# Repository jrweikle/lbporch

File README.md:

# lbporch
This is my attempt to clone the Orch90 board for the TRS80 Model 3 and 4 
it is a work in progress it has not been tested on a machine at this time

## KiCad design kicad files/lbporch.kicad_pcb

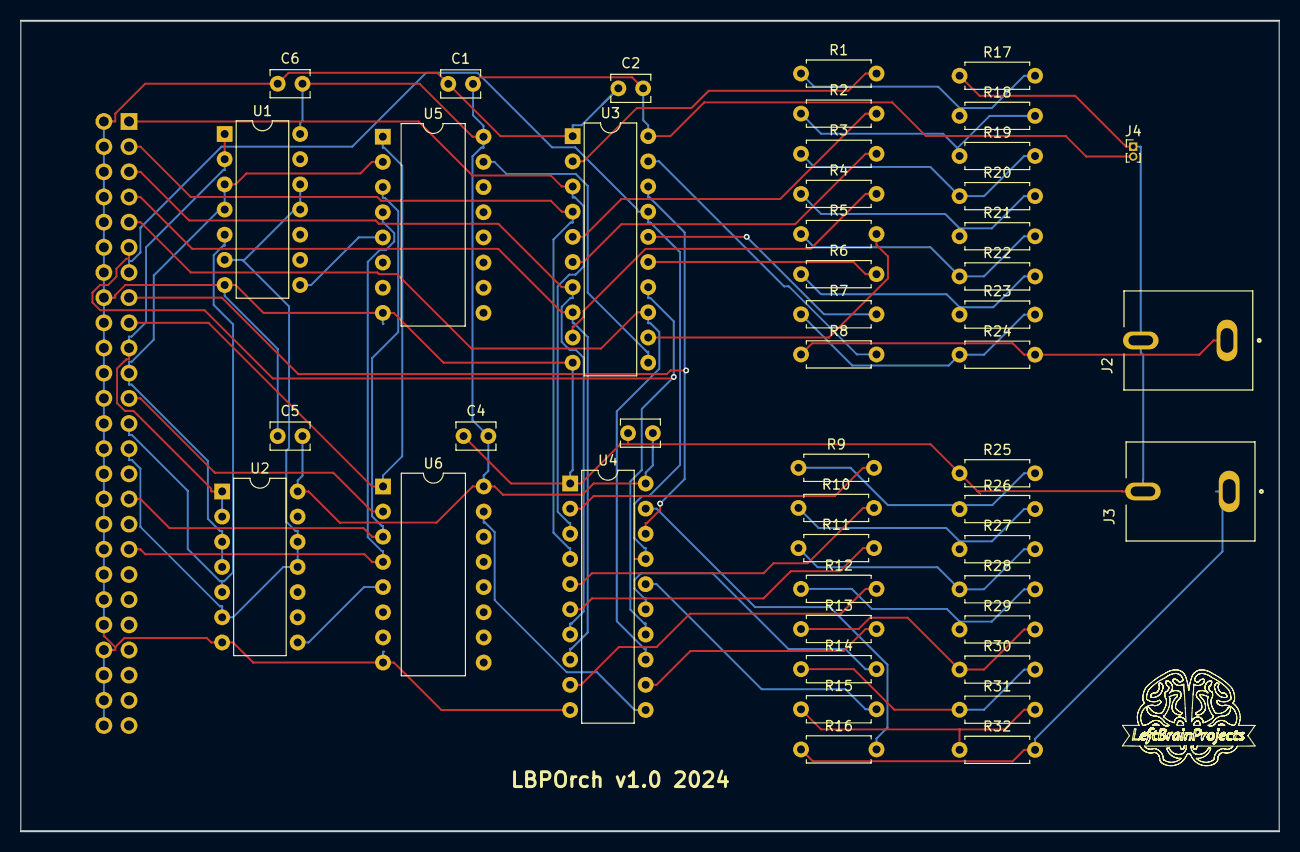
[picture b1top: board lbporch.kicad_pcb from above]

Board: 2 copper layers, 127.0 x 81.8 mm, 48 parts (1 on the bottom side), 54 nets.

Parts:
C1, C2, C3, C4, C5, C6: 0.1; C_Disc_D3.8mm_W2.6mm_P2.50mm
J1: Conn_02x25_Odd_Even; PinHeader_2x25_P2.54mm_Vertical
J2, J3: Conn_Coaxial; CUI_RCJ-054
J4: Conn_01x02_Pin; PinHeader_1x02_P1.00mm_Vertical
R1, R2, R3, R4, R5, R6, R7, R8, R9, R10, R11, R12, R13, R14, R15, R16: 20k; R_Axial_DIN0207_L6.3mm_D2.5mm_P7.62mm_Horizontal
R17, R18, R19, R20, R21, R22, R23, R24, R25, R26, R27, R28, R29, R30, R31, R32: 10k; R_Axial_DIN0207_L6.3mm_D2.5mm_P7.62mm_Horizontal
U1, U2: 74LS30; DIP-14_W7.62mm
U3, U4: 74LS374; DIP-20_W7.62mm
U5, U6: 74LS138; DIP-16_W10.16mm

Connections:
+5V: C1.2, C2.2, C3.2, C4.2, C5.2, C6.2, J4.2, U1.14 (Vcc), U2.14 (Vcc), U3.20 (VCC), U4.20 (VCC), U5.16 (VCC), U6.16 (VCC)
/A0: J1.17, U5.1 (A0), U6.1 (A0)
/A1: J1.19, U1.1, U1.2, U2.1, U2.2
/A2: J1.21, U1.3, U1.4, U2.3, U2.4, U5.2 (A1)
/A3: J1.23, U6.2 (A1)
/A4: J1.25, U1.5, U2.5
/A5: J1.27, U1.6, U1.11, U1.12, U2.6, U2.11, U2.12
/A7: J1.31, U5.3 (A2), U6.3 (A2)
/D0: J1.1, U3.3 (D0), U4.3 (D0)
/D1: J1.3, U3.4 (D1), U4.4 (D1)
/D2: J1.5, U3.7 (D2), U4.7 (D2)
/D3: J1.7, U3.8 (D3), U4.8 (D3)
/D4: J1.9, U3.13 (D4), U4.13 (D4)
/D5: J1.11, U3.14 (D5), U4.14 (D5)
/D6: J1.13, U3.17 (D6), U4.17 (D6)
/D7: J1.15, U3.18 (D7), U4.18 (D7)
/XOUT: J1.35, U5.4 (E1), U6.4 (E1)
GND: C1.1, C2.1, C3.1, C4.1, C5.1, C6.1, J1.2, J1.4, J1.6, J1.8, J1.10, J1.12, J1.14, J1.16, J1.18, J1.20, J1.22, J1.24, J1.26, J1.28, J1.30, J1.32, J1.34, J1.36, J1.38, J1.40, J1.42, J1.44, J1.46, J1.48, J1.50, J2.2 (Ext), J3.2 (Ext), J4.1, R17.1, R25.1, U1.7 (GND), U2.7 (GND), U3.1 (OE), U3.10 (GND), U4.1 (OE), U4.10 (GND), U5.8 (GND), U6.8 (GND)
unnamed: J2.1 (In), R8.1, R24.2
unnamed: J3.1 (In), R16.1, R32.2
unnamed: R1.1, R17.2, R18.1
unnamed: R10.1, R26.2, R27.1
unnamed: R11.1, R27.2, R28.1
unnamed: R12.1, R28.2, R29.1
unnamed: R13.1, R29.2, R30.1
unnamed: R14.1, R30.2, R31.1
unnamed: R15.1, R31.2, R32.1
unnamed: R2.1, R18.2, R19.1
unnamed: R3.1, R19.2, R20.1
unnamed: R4.1, R20.2, R21.1
unnamed: R5.1, R21.2, R22.1
unnamed: R6.1, R22.2, R23.1
unnamed: R7.1, R23.2, R24.1
unnamed: R9.1, R25.2, R26.1
unnamed: U3.11 (Cp), U5.15 (O0)
unnamed: R1.2, U3.2 (O0)
unnamed: R2.2, U3.5 (O1)
unnamed: R3.2, U3.6 (O2)
unnamed: R4.2, U3.9 (O3)
unnamed: R5.2, U3.12 (O4)
unnamed: R6.2, U3.15 (O5)
unnamed: R7.2, U3.16 (O6)
unnamed: R8.2, U3.19 (O7)
unnamed: U4.11 (Cp), U6.15 (O0)
unnamed: R9.2, U4.2 (O0)
unnamed: R10.2, U4.5 (O1)
unnamed: R11.2, U4.6 (O2)
unnamed: R12.2, U4.9 (O3)
unnamed: R13.2, U4.12 (O4)
unnamed: R14.2, U4.15 (O5)
unnamed: R15.2, U4.16 (O6)
unnamed: R16.2, U4.19 (O7)
unnamed: U1.8, U5.5 (E2)
unnamed: U2.8, U6.5 (E2)

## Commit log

2024-05-30 First set of PCB Boards
2024-05-30 Create kicad
2024-05-30 Update and rename lbporch.kicad_pcb to lbporch.kicad/kicad_pcb
2024-05-30 Delete lbporch.kicad_pcb
    moved to new directory
2024-05-30 Delete lbporch.kicad_prl
    moved to new directory
2024-05-30 Delete lbporch.kicad_pro
    move to new directory
2024-06-17 Create gerbers
2024-06-17 Create kicad files
